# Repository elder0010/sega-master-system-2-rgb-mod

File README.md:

# Sega Master System 2 RGB PCB Mod with optional Sync Stripper
This is a RGB mod board for Sega Master System 2 with optional support for LM1881 sync stripper module.
It fits the RF modulator space, so you don't have to drill holes in your console.

Included in this repository:

  - Eagle project (schematics + board)
  - Gerber files (in directory CAMOutputs)

# Required parts list
In addition to the board, you will need:

 - 4x 220 μF 25v capacitors (C1/C4)
 - 1x 10 μF 25v capacitors (C5)
 - 5x 75 ohm resistors (R1/R5)
 - 7 pin mini din connector

# Optional parts list
If you wish to add sync separation capability to the board you will need:

 - LM1881N chip (IC1)
 - 2x 0.1 μF ceramic capacitors (C6/C7)
 - 1x 75 ohm resistor (R6)

# Wiring
Wire the composite, red, green, blue, audio, ground and VCC signals from the console on the input pads.
Instructions for locating the signals on the console can be found here: [Master System II RGB/S-Video Modification](http://www.smspower.org/masterful/rgb.html)

Wire the output signals to the mini din connector. The output pads Oe, Bu, Vs, Cs are for the LM1881N chip.

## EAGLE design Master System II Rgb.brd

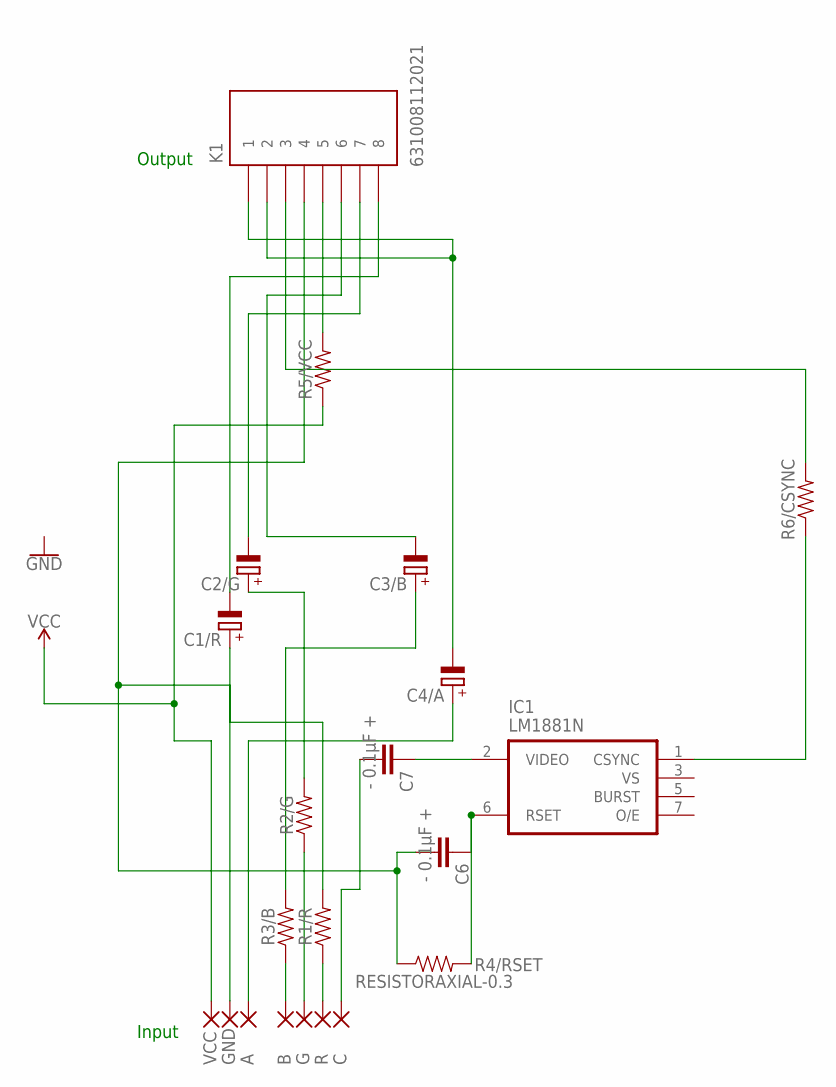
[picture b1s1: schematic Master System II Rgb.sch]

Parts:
A: WIREPADSMD2,54-5,08; SMD2,54-5,08
B: WIREPADSMD2,54-5,08; SMD2,54-5,08
C: WIREPADSMD2,54-5,08; SMD2,54-5,08
C1/R, C2/G, C3/B, C4/A: CPOL-EUE2.5-6; E2,5-6
C6, C7: - 0.1μF +; CAP-PTH-2.54
G: WIREPADSMD2,54-5,08; SMD2,54-5,08
GND: WIREPADSMD2,54-5,08; SMD2,54-5,08
IC1: LM1881N; DIL08
K1: 631008112021
R: WIREPADSMD2,54-5,08; SMD2,54-5,08
R1/R, R2/G, R3/B, R5/VCC, R6/CSYNC: AXIAL-0.3
R4/RSET: RESISTORAXIAL-0.3; AXIAL-0.3
VCC: WIREPADSMD2,54-5,08; SMD2,54-5,08

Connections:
GND: IC1.4 (GND)
unnamed: C6.2, GND.1, K1.7 (4), R4/RSET.P$1 (1)
unnamed: C4/A.-, K1.1 (2), K1.2 (1)
unnamed: C1/R.+, R1/R.P$2 (2)
unnamed: C1/R.-, K1.6 (8)
unnamed: C2/G.+, R2/G.P$2 (2)
unnamed: C2/G.-, K1.4 (7)
unnamed: C3/B.+, R3/B.P$2 (2)
unnamed: C3/B.-, K1.8 (6)
unnamed: A.1, C4/A.+
unnamed: IC1.1 (CSYNC), R6/CSYNC.P$1 (1)
unnamed: C.1, C7.2
unnamed: K1.3 (5), R5/VCC.P$2 (2)
unnamed: R.1, R1/R.P$1 (1)
unnamed: C6.1, IC1.6 (RSET), R4/RSET.P$2 (2)
unnamed: G.1, R2/G.P$1 (1)
unnamed: B.1, R3/B.P$1 (1)
unnamed: K1.5 (3), R6/CSYNC.P$2 (2)
unnamed: C7.1, IC1.2 (VIDEO)
VCC: IC1.8 (VCC), R5/VCC.P$1 (1), VCC.1

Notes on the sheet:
Input
Output

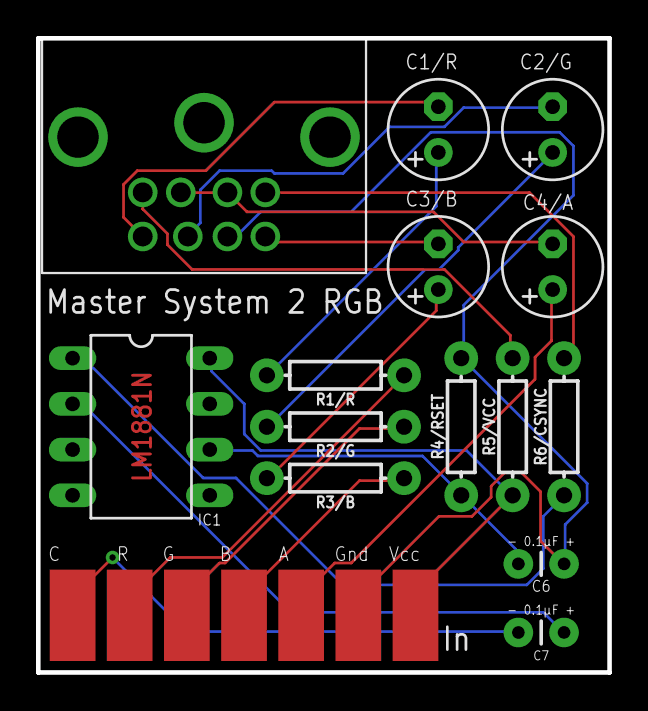
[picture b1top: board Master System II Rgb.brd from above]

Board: 2 copper layers, 31.7 x 35.2 mm, 21 parts (0 on the bottom side), 19 nets.

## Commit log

2024-07-14 First import

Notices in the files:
parts and their libraries:
SparkFun-Resistors: Licensing: Creative Commons ShareAlike 4.0 International - https://creativecommons.org/licenses/by-sa/4.0
Wuerth_Elektronik_eiCan_Communication_Co: Copyright: Würth Elektronik
